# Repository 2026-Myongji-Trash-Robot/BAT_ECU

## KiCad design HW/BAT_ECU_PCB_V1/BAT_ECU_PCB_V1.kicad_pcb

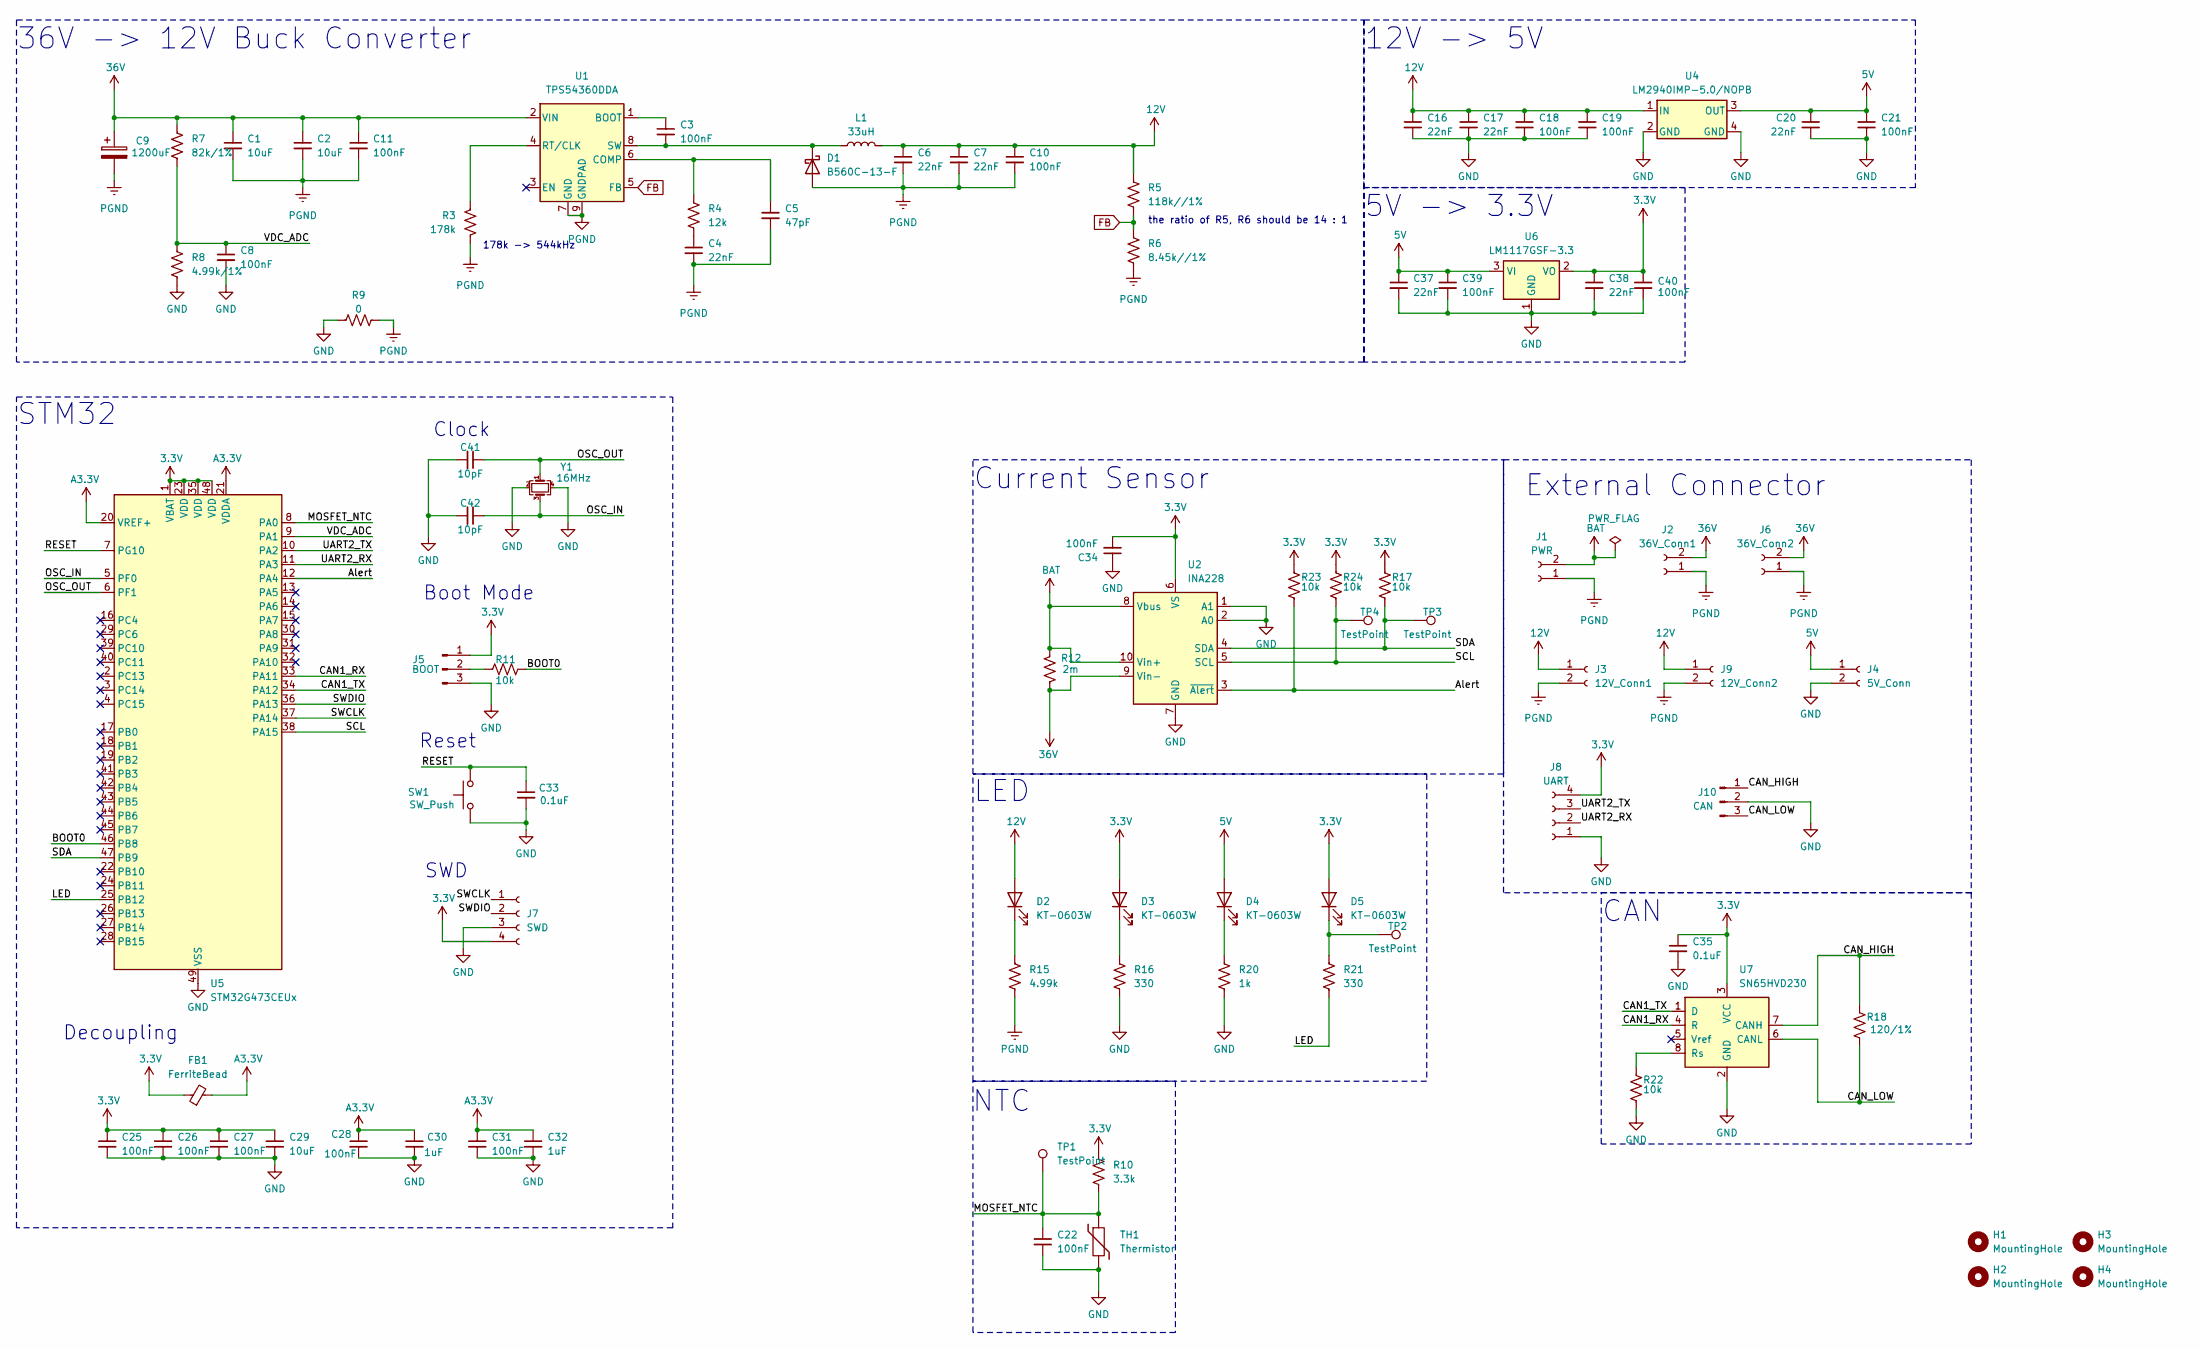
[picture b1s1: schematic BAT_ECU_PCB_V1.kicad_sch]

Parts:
C1, C2: 10uF; C_1210_3225Metric; LCSC C576517
C3, C8, C10, C18, C19, C21, C22, C39, C40: 100nF; C_0603_1608Metric; LCSC C14663
C4: 22nF; C_0603_1608Metric; LCSC C21122
C5: 47pF; C_0603_1608Metric; LCSC C1671
C6, C7, C16, C17, C20, C37, C38: 22nF; C_0805_2012Metric; LCSC C45783
C9: 1200uF; CP_Radial_D18.0mm_P7.50mm; LCSC C2835718
C11: 100nF; C_0805_2012Metric; LCSC C28233
C25, C26, C27, C28, C31, C34: 100nF; C_0603_1608Metric
C29: 10uF; C_0603_1608Metric
C30, C32: 1uF; C_0603_1608Metric
C33, C35: 0.1uF; C_0603_1608Metric
C41, C42: 10pF; C_0402_1005Metric_Pad0.74x0.62mm_HandSolder; LCSC C32949
D1: B560C-13-F; D_SMC; LCSC C85100
D2, D3, D4, D5: KT-0603W; LED_0603_1608Metric; LCSC C2290
FB1: FerriteBead; L_0603_1608Metric; LCSC C1002
H1, H2, H3, H4: MountingHole; MountingHole_3.2mm_M3_DIN965
J1: PWR; AMASS_XT60PW-M_1x02_P7.20mm_Horizontal
J2: 36V_Conn1; AMASS_XT60PW-M_1x02_P7.20mm_Horizontal; LCSC C98732
J3: 12V_Conn1; Wago_734-162_1x02_P3.50mm_Horizontal
J4: 5V_Conn; Wago_734-162_1x02_P3.50mm_Horizontal
J5: BOOT; PinHeader_1x03_P2.54mm_Vertical
J6: 36V_Conn2; AMASS_XT60PW-M_1x02_P7.20mm_Horizontal; LCSC C98732
J7: SWD; PinHeader_1x04_P2.54mm_Horizontal
J8: UART; PinHeader_1x04_P2.54mm_Horizontal
J9: 12V_Conn2; Wago_734-162_1x02_P3.50mm_Horizontal
J10: CAN; Wago_734-163_1x03_P3.50mm_Horizontal
L1: 33uH; L_SXN_SMDRI127; LCSC C9400
R3: 178k; R_0603_1608Metric; LCSC C22823
R4: 12k; R_0603_1608Metric; LCSC C22790
R5: 118k//1%; R_0603_1608Metric; LCSC C25806
R6: 8.45k//1%; R_0603_1608Metric; LCSC C14892
R7: 82k/1%; R_0603_1608Metric; LCSC C137678
R8: 4.99k/1%; R_0603_1608Metric; LCSC C23046
R9: 0; R_1206_3216Metric; LCSC C17888
R10: 3.3k; R_0603_1608Metric; LCSC C22978
R11, R17, R22, R23, R24: 10k; R_0603_1608Metric; LCSC C15401
R12: 2m; R_2512_6332Metric_Pad1.40x3.35mm_HandSolder; LCSC C500614
R15: 4.99k; R_0603_1608Metric; LCSC C23046
R16, R21: 330; R_0603_1608Metric; LCSC C23138
R18: 120/1%; R_0603_1608Metric; LCSC C22787
R20: 1k; R_0603_1608Metric; LCSC C21190
SW1: SW_Push; SW_PUSH_6mm_H7.3mm; LCSC C255812
TH1: Thermistor; R_0603_1608Metric; LCSC C142556
TP1, TP2, TP3, TP4: TestPoint; TestPoint_Pad_D1.0mm
U1: TPS54360DDA; TI_SO-PowerPAD-8_ThermalVias; LCSC C524806
U2: INA228; VSSOP-10_3x3mm_P0.5mm; LCSC C5214669
U4: LM2940IMP-5.0/NOPB; SOT-223; LCSC C13991
U5: STM32G473CEUx; QFN-48-1EP_7x7mm_P0.5mm_EP5.6x5.6mm; LCSC C1342773
U6: LM1117GSF-3.3; SOT-23; LCSC C481677
U7: SN65HVD230; SOIC-8_3.9x4.9mm_P1.27mm
Y1: 16MHz; Crystal_SMD_3225-4Pin_3.2x2.5mm; LCSC C13738

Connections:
3.3V: C25.1, C26.1, C27.1, C29.1, C34.2, C35.1, C38.1, C40.1, D3.2 (A), D5.2 (A), FB1.1, J5.1, J7.4, J8.4, R10.1, R17.2, R23.2, R24.2, U2.6 (VS), U5.1 (VBAT), U5.23 (VDD), U5.35 (VDD), U5.48 (VDD), U6.2 (VO), U7.3 (VCC)
12V: C6.1, C7.1, C10.1, C16.1, C17.1, C18.1, C19.1, D2.2 (A), J3.1, J9.1, L1.2, R5.1, U4.1 (IN)
36V: C1.1, C2.1, C9.1, C11.1, J2.2, J6.2, R7.1, R12.2, U1.2 (VIN), U2.9 (Vin-)
/Alert: R23.1, U2.3 (~Alert), U5.12 (PA4)
/BOOT0: R11.2, U5.46 (PB8)
/CAN1_RX: U5.33 (PA11), U7.4 (R)
/CAN1_TX: U5.34 (PA12), U7.1 (D)
/CAN_HIGH: J10.1, R18.2, U7.7 (CANH)
/CAN_LOW: J10.3, R18.1, U7.6 (CANL)
/LED: R21.2, U5.25 (PB12)
/MOSFET_NTC: C22.1, R10.2, TH1.1, TP1.1, U5.8 (PA0)
/OSC_IN: C42.1, U5.5 (PF0), Y1.3
/OSC_OUT: C41.1, U5.6 (PF1), Y1.1
/RESET: C33.1, SW1.2, U5.7 (PG10)
/SCL: R24.1, TP4.1, U2.5 (SCL), U5.38 (PA15)
/SDA: R17.1, TP3.1, U2.4 (SDA), U5.47 (PB9)
/SWCLK: J7.1, U5.37 (PA14)
/SWDIO: J7.2, U5.36 (PA13)
/UART2_RX: J8.2, U5.11 (PA3)
/UART2_TX: J8.3, U5.10 (PA2)
/VDC_ADC: C8.1, R7.2, R8.1, U5.9 (PA1)
A3.3V: C28.1, C30.1, C31.1, C32.1, FB1.2, U5.20 (VREF+), U5.21 (VDDA)
BAT: J1.2, R12.1, U2.8 (Vbus), U2.10 (Vin+)
FB: R5.2, R6.1, U1.5 (FB)
unnamed: C4.1, R4.2
unnamed: C3.2, D1.1 (K), L1.1, U1.8 (SW)
unnamed: D2.1 (K), R15.1
unnamed: D3.1 (K), R16.1
unnamed: D4.1 (K), R20.1
unnamed: D5.1 (K), R21.1, TP2.1
unnamed: J5.2, R11.1
unnamed: C3.1, U1.1 (BOOT)
unnamed: C5.1, R4.1, U1.6 (COMP)
unnamed: R3.1, U1.4 (RT/CLK)
unnamed: R22.2, U7.8 (Rs)
PGND: C1.2, C2.2, C4.2, C5.2, C6.2, C7.2, C9.2, C10.2, C11.2, D1.2 (A), J1.1, J2.1, J3.2, J6.1, J9.2, R3.2, R6.2, R9.2, R15.2, U1.7 (GND), U1.9 (GNDPAD)

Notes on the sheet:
Current Sensor
STM32
Reset
External Connector
NTC
CAN
36V -> 12V Buck Converter
12V -> 5V
Decoupling
5V -> 3.3V
SWD
Boot Mode
178k -> 544kHz
Clock
LED
the ratio of R5, R6 should be 14 : 1

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
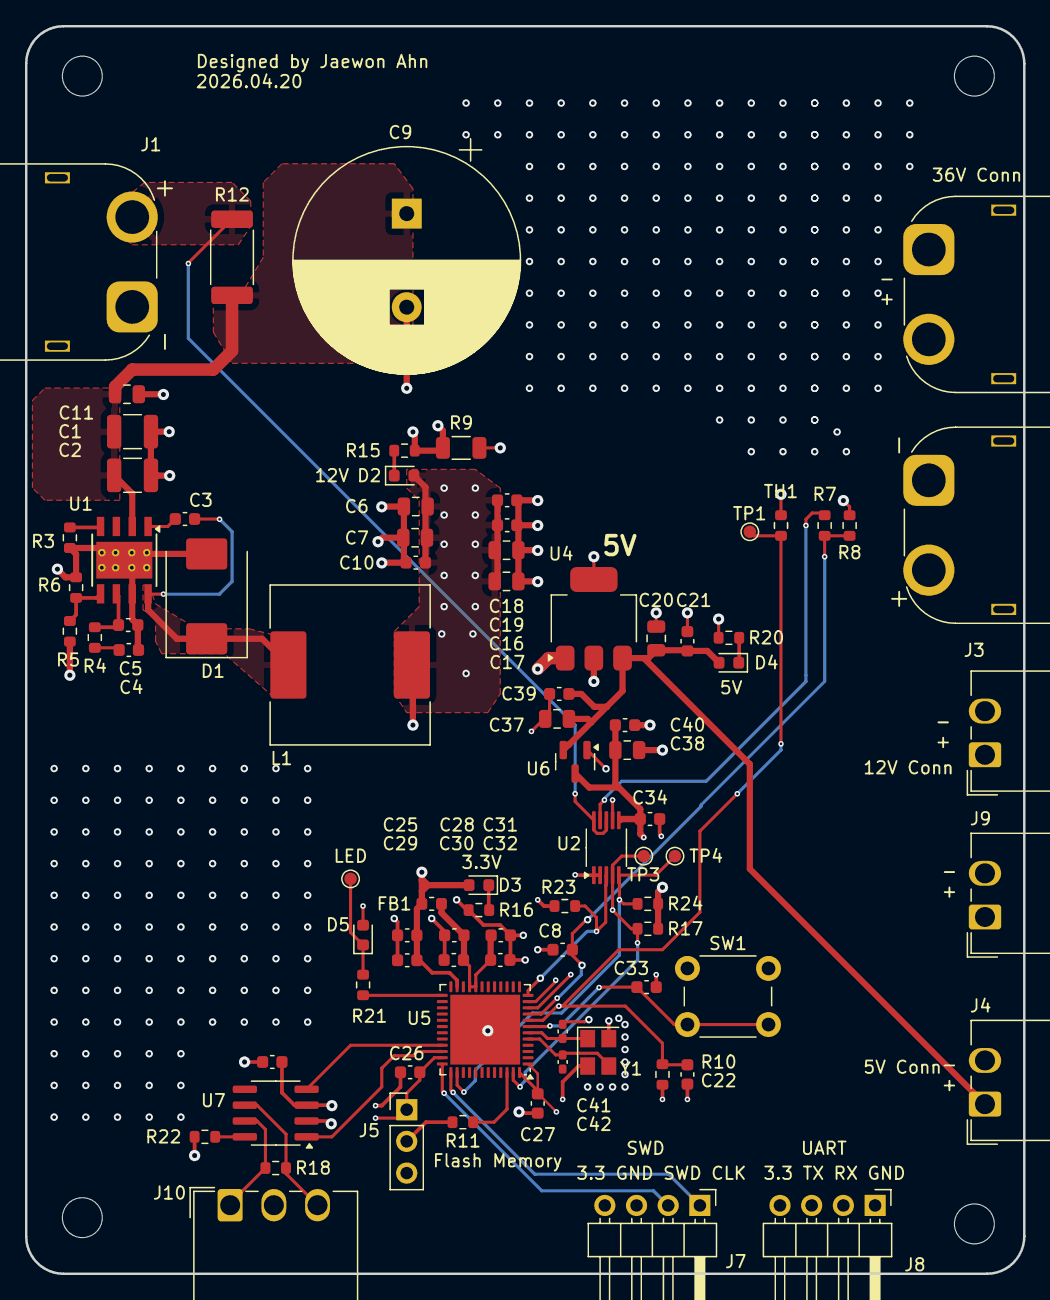
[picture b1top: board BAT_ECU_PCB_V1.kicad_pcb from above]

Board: 4 copper layers, 80.0 x 100.0 mm, 88 parts (0 on the bottom side), 38 nets.

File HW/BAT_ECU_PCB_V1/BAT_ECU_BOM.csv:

Designator,Qty,Comment,Footprint,JLCPCB Part #£¨optional£©
"C1,C2",2,10uF,Capacitor_SMD:C_1210_3225Metric,C576517
"C3,C8,C10,C18,C19,C21,C22,C25,C26,C27,C28,C31,C34,C39,C40",15,100nF,Capacitor_SMD:C_0603_1608Metric,C14663
C4,1,22nF,Capacitor_SMD:C_0603_1608Metric,C21122
C5,1,47pF,Capacitor_SMD:C_0603_1608Metric,C1671
"C6,C7,C16,C17,C20,C37,C38",7,22nF,Capacitor_SMD:C_0805_2012Metric,C45783
C9,1,1200uF,Capacitor_THT:CP_Radial_D18.0mm_P7.50mm,C2835718
C11,1,100nF,Capacitor_SMD:C_0805_2012Metric,C28233
C29,1,10uF,Capacitor_SMD:C_0603_1608Metric,
"C30,C32",2,1uF,Capacitor_SMD:C_0603_1608Metric,
"C33,C35",2,0.1uF,Capacitor_SMD:C_0603_1608Metric,
"C41,C42",2,10pF,Capacitor_SMD:C_0603_1608Metric,C32949
D1,1,B560C-13-F,Diode_SMD:D_SMC,C85100
"D2,D3,D4,D5",4,KT-0603W,LED_SMD:LED_0603_1608Metric,C2290
FB1,1,FerriteBead,Inductor_SMD:L_0603_1608Metric,C1002
J1,1,PWR,Connector_AMASS:AMASS_XT60PW-M_1x02_P7.20mm_Horizontal,C98732
J2,1,36V_Conn1,Connector_AMASS:AMASS_XT60PW-M_1x02_P7.20mm_Horizontal,C98732
J3,1,12V_Conn1,Connector_Wago:Wago_734-162_1x02_P3.50mm_Horizontal,
J4,1,5V_Conn,Connector_Wago:Wago_734-162_1x02_P3.50mm_Horizontal,
J5,1,BOOT,Connector_PinHeader_2.54mm:PinHeader_1x03_P2.54mm_Vertical,
J6,1,36V_Conn2,Connector_AMASS:AMASS_XT60PW-M_1x02_P7.20mm_Horizontal,C98732
J7,1,SWD,Connector_PinHeader_2.54mm:PinHeader_1x04_P2.54mm_Horizontal,
J8,1,UART,Connector_PinHeader_2.54mm:PinHeader_1x04_P2.54mm_Horizontal,
J9,1,12V_Conn2,Connector_Wago:Wago_734-162_1x02_P3.50mm_Horizontal,
J10,1,CAN,Connector_Wago:Wago_734-163_1x03_P3.50mm_Horizontal,
L1,1,33uH,Inductor_SMD:L_SXN_SMDRI127,C9400
R3,1,178k,Resistor_SMD:R_0603_1608Metric,C22823
R4,1,12k,Resistor_SMD:R_0603_1608Metric,C22790
R5,1,118k//1%,Resistor_SMD:R_0603_1608Metric,C25806
R6,1,8.45k//1%,Resistor_SMD:R_0603_1608Metric,C14892
R7,1,82k/1%,Resistor_SMD:R_0603_1608Metric,C137678
R8,1,4.99k/1%,Resistor_SMD:R_0603_1608Metric,C23046
R9,1,0,Resistor_SMD:R_1206_3216Metric,C17888
R10,1,3.3k,Resistor_SMD:R_0603_1608Metric,C22978
"R11,R17,R22,R23,R24",5,10k,Resistor_SMD:R_0603_1608Metric,C15401
R12,1,2m,Resistor_SMD:R_2512_6332Metric_Pad1.40x3.35mm_HandSolder,C500614
R15,1,4.99k,Resistor_SMD:R_0603_1608Metric,C23046
"R16,R21",2,330,Resistor_SMD:R_0603_1608Metric,C23138
R18,1,120/1%,Resistor_SMD:R_0603_1608Metric,C22787
R20,1,1k,Resistor_SMD:R_0603_1608Metric,C21190
SW1,1,SW_Push,Button_Switch_THT:SW_PUSH_6mm_H7.3mm,C255812
TH1,1,Thermistor,Resistor_SMD:R_0603_1608Metric,C142556
U1,1,TPS54360DDA,Package_SO:TI_SO-PowerPAD-8_ThermalVias,C524806 
U2,1,INA228,Package_SO:VSSOP-10_3x3mm_P0.5mm,C5214669
U4,1,LM2940IMP-5.0/NOPB,Package_TO_SOT_SMD:SOT-223,C13991
U5,1,STM32G473CEUx,Package_DFN_QFN:QFN-48-1EP_7x7mm_P0.5mm_EP5.6x5.6mm,C1342773
U6,1,LM1117GSF-3.3,Package_TO_SOT_SMD:SOT-23,C481677
U7,1,SN65HVD230,Package_SO:SOIC-8_3.9x4.9mm_P1.27mm,C12084
Y1,1,16MHz,Crystal:Crystal_SMD_3225-4Pin_3.2x2.5mm,C13738
